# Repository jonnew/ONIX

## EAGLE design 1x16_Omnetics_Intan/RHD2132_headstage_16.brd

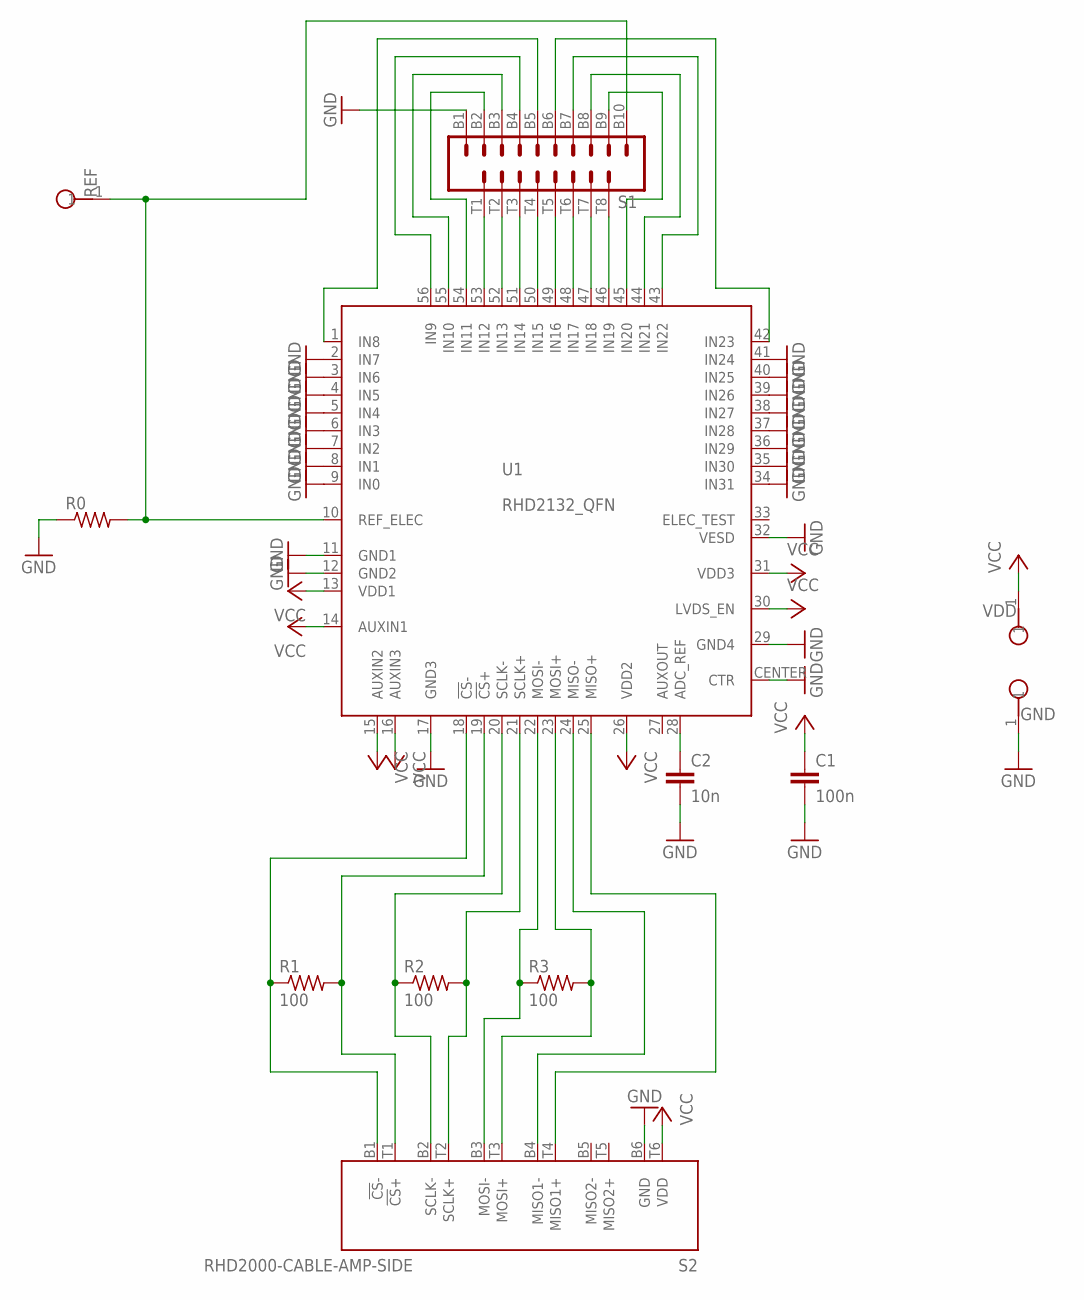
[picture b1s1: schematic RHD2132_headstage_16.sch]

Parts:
C1: 100n; 0402
C2: 10n; 0402
GND: TESTPOINT_SMALL
R0: R_0402; 0402
R1, R2, R3: 100; 0402
REF: TESTPOINT_SMALL
S1: OMNETICS_A79041
S2: RHD2000-CABLE-AMP-SIDE; OMNETICS_PZN-12-AA
U1: RHD2132_QFN; QFN56_8_X_8_LARGE
VDD: TESTPOINT_SMALL

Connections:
GND: C1.2, C2.2, GND.1, R0.1, S1.B1, S2.B6 (GND), U1.2 (IN7), U1.3 (IN6), U1.4 (IN5), U1.5 (IN4), U1.6 (IN3), U1.7 (IN2), U1.8 (IN1), U1.9 (IN0), U1.11 (GND1), U1.12 (GND2), U1.17 (GND3), U1.29 (GND4), U1.32 (VESD), U1.34 (IN31), U1.35 (IN30), U1.36 (IN29), U1.37 (IN28), U1.38 (IN27), U1.39 (IN26), U1.40 (IN25), U1.41 (IN24), U1.CENTER (CTR)
unnamed: R0.2, REF.1, S1.B10, U1.10 (REF_ELEC)
unnamed: S1.B6, U1.42 (IN23)
unnamed: R1.1, S2.B1 (!CS!-), U1.18 (!CS!-)
unnamed: S1.T4, U1.50 (IN15)
unnamed: S1.T3, U1.51 (IN14)
unnamed: S1.T2, U1.52 (IN13)
unnamed: S1.B4, U1.56 (IN9)
unnamed: S1.B3, U1.55 (IN10)
unnamed: S1.B2, U1.54 (IN11)
unnamed: S1.T1, U1.53 (IN12)
unnamed: S1.T5, U1.49 (IN16)
unnamed: S1.T6, U1.48 (IN17)
unnamed: S1.T7, U1.47 (IN18)
unnamed: S1.T8, U1.46 (IN19)
unnamed: S1.B9, U1.45 (IN20)
unnamed: S1.B8, U1.44 (IN21)
unnamed: S1.B7, U1.43 (IN22)
unnamed: S1.B5, U1.1 (IN8)
unnamed: R1.2, S2.T1 (!CS!+), U1.19 (!CS!+)
unnamed: R2.1, S2.B2 (SCLK-), U1.20 (SCLK-)
unnamed: R2.2, S2.T2 (SCLK+), U1.21 (SCLK+)
unnamed: R3.1, S2.B3 (MOSI-), U1.22 (MOSI-)
unnamed: R3.2, S2.T3 (MOSI+), U1.23 (MOSI+)
unnamed: S2.B4 (MISO1-), U1.24 (MISO-)
unnamed: S2.T4 (MISO1+), U1.25 (MISO+)
unnamed: C2.1, U1.28 (ADC_REF)
VCC: C1.1, S2.T6 (VDD), U1.13 (VDD1), U1.14 (AUXIN1), U1.15 (AUXIN2), U1.16 (AUXIN3), U1.26 (VDD2), U1.30 (LVDS_EN), U1.31 (VDD3), VDD.1

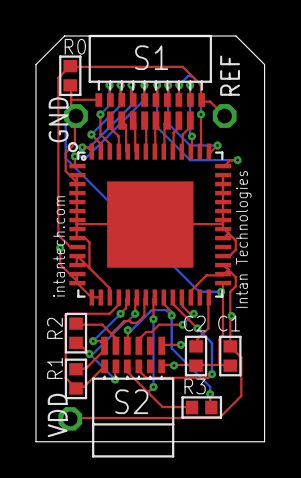
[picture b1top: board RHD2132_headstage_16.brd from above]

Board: 4 copper layers, 12.7 x 22.5 mm, 12 parts (0 on the bottom side), 28 nets.

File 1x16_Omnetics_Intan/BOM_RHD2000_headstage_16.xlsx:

Bill of Materials |  | RHD2000 Headstage Board 16 |  | Intan Technologies, LLC
Part | Value | Device | Package | Digi-Key part number | Notes
C1 | 100 nF (0.1 uF) | ceramic capacitor (25 V) | 0402 | 445-4964-1-ND
C2 | 10 nF (10000 pF) | ceramic capacitor (25 V) | 0402 | 490-1312-1-ND
R0 | 0 | resistor | 0402 | P0.0JCT-ND
R1 | 100 | resistor | 0402 | P100JCT-ND
R2 | 100 | resistor | 0402 | P100JCT-ND
R3 | 100 | resistor | 0402 | P100JCT-ND
S1 | NSD-18-AA-GS | nano strip connector | 18-pin, 2 guides | Omnetics A79041-001
S2 | PZN-12-AA | polarized nano connector | polarized 12-pin | Omnetics A79623-001
U1 | RHD2132 | 32-channel amplifier chip | QFN-56L | Intan RHD2132

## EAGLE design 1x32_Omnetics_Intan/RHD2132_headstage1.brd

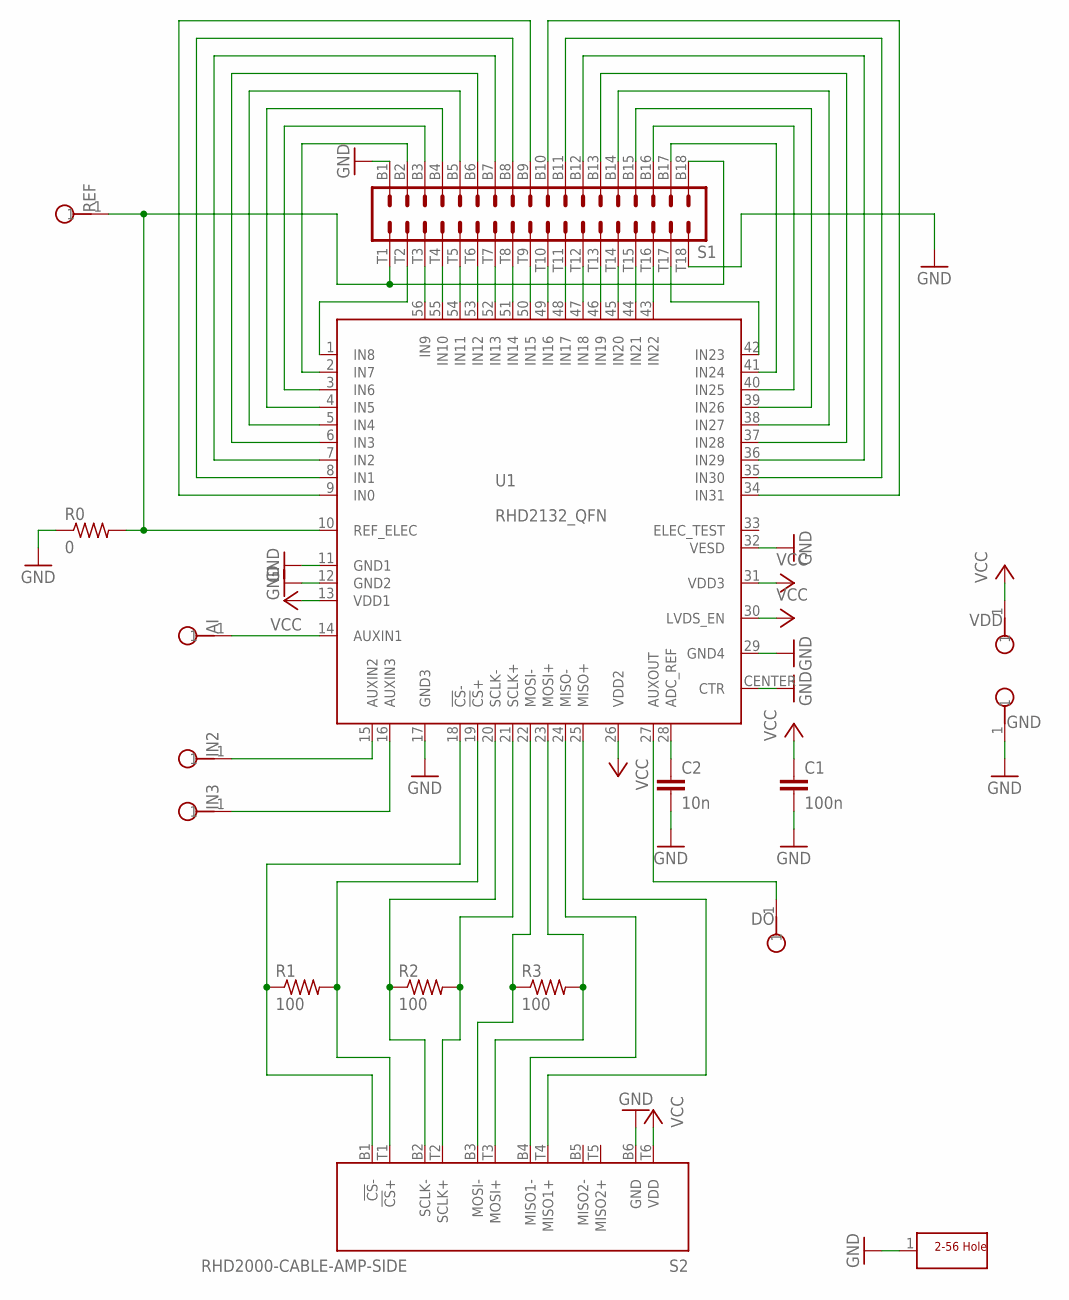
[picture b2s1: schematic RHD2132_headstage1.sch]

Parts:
AI: TESTPOINT_SMALL
C1: 100n; 0402
C2: 10n; 0402
DO: TESTPOINT_SMALL
GND: TESTPOINT_SMALL
H1: SCREW_HOLE_2-56
IN2, IN3: TESTPOINT_SMALL
R0: 0; 0402
R1, R2, R3: 100; 0402
REF: TESTPOINT_SMALL
S1: OMNETICS_A79025
S2: RHD2000-CABLE-AMP-SIDE; OMNETICS_PZN-12-AA
U1: RHD2132_QFN; QFN56_8_X_8_LARGE
VDD: TESTPOINT_SMALL

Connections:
GND: C1.2, C2.2, GND.1, H1.1, R0.1, S1.B1, S1.T18, S2.B6 (GND), U1.11 (GND1), U1.12 (GND2), U1.17 (GND3), U1.29 (GND4), U1.32 (VESD), U1.CENTER (CTR)
unnamed: R0.2, REF.1, S1.B18, S1.T1, U1.10 (REF_ELEC)
unnamed: S1.B3, U1.3 (IN6)
unnamed: S1.B2, U1.2 (IN7)
unnamed: S1.B4, U1.4 (IN5)
unnamed: S1.B5, U1.5 (IN4)
unnamed: S1.B6, U1.6 (IN3)
unnamed: S1.B7, U1.7 (IN2)
unnamed: S1.B8, U1.8 (IN1)
unnamed: S1.B9, U1.9 (IN0)
unnamed: S1.B10, U1.34 (IN31)
unnamed: R1.1, S2.B1 (!CS!-), U1.18 (!CS!-)
unnamed: S1.B17, U1.41 (IN24)
unnamed: S1.B16, U1.40 (IN25)
unnamed: S1.B15, U1.39 (IN26)
unnamed: S1.B14, U1.38 (IN27)
unnamed: S1.B13, U1.37 (IN28)
unnamed: S1.B12, U1.36 (IN29)
unnamed: S1.B11, U1.35 (IN30)
unnamed: S1.T9, U1.50 (IN15)
unnamed: S1.T8, U1.51 (IN14)
unnamed: S1.T7, U1.52 (IN13)
unnamed: S1.T3, U1.56 (IN9)
unnamed: S1.T4, U1.55 (IN10)
unnamed: S1.T5, U1.54 (IN11)
unnamed: S1.T6, U1.53 (IN12)
unnamed: S1.T10, U1.49 (IN16)
unnamed: S1.T11, U1.48 (IN17)
unnamed: S1.T12, U1.47 (IN18)
unnamed: S1.T13, U1.46 (IN19)
unnamed: S1.T14, U1.45 (IN20)
unnamed: S1.T15, U1.44 (IN21)
unnamed: S1.T16, U1.43 (IN22)
unnamed: S1.T2, U1.1 (IN8)
unnamed: S1.T17, U1.42 (IN23)
unnamed: R1.2, S2.T1 (!CS!+), U1.19 (!CS!+)
unnamed: R2.1, S2.B2 (SCLK-), U1.20 (SCLK-)
unnamed: R2.2, S2.T2 (SCLK+), U1.21 (SCLK+)
unnamed: R3.1, S2.B3 (MOSI-), U1.22 (MOSI-)
unnamed: R3.2, S2.T3 (MOSI+), U1.23 (MOSI+)
unnamed: S2.B4 (MISO1-), U1.24 (MISO-)
unnamed: S2.T4 (MISO1+), U1.25 (MISO+)
unnamed: C2.1, U1.28 (ADC_REF)
unnamed: DO.1, U1.27 (AUXOUT)
unnamed: AI.1, U1.14 (AUXIN1)
unnamed: IN2.1, U1.15 (AUXIN2)
unnamed: IN3.1, U1.16 (AUXIN3)
VCC: C1.1, S2.T6 (VDD), U1.13 (VDD1), U1.26 (VDD2), U1.30 (LVDS_EN), U1.31 (VDD3), VDD.1

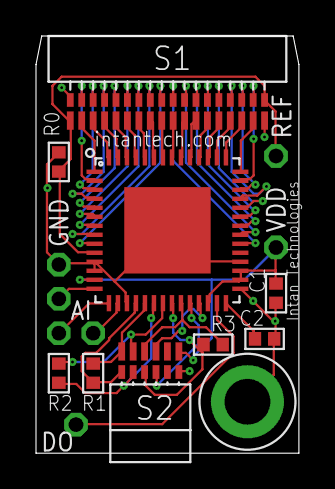
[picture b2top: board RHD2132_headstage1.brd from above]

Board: 4 copper layers, 14.6 x 23.2 mm, 17 parts (0 on the bottom side), 48 nets.

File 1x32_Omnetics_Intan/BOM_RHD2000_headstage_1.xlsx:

Bill of Materials |  | RHD2000 Headstage Board 1 |  | Intan Technologies, LLC
Part | Value | Device | Package | Digi-Key part number | Notes
C1 | 100 nF (0.1 uF) | ceramic capacitor (25 V) | 0402 | 445-4964-1-ND
C2 | 10 nF (10000 pF) | ceramic capacitor (25 V) | 0402 | 490-1312-1-ND
R0 | 0 | resistor | 0402 | P0.0JCT-ND
R1 | 100 | resistor | 0402 | P100JCT-ND
R2 | 100 | resistor | 0402 | P100JCT-ND
R3 | 100 | resistor | 0402 | P100JCT-ND
S1 | NSD-36-AA-GS | nano strip connector | 36-pin, 4 guides | Omnetics A79025-001
S2 | PZN-12-AA | polarized nano connector | polarized 12-pin | Omnetics A79623-001
U1 | RHD2132 or RHD2216 | 32-channel amplifier chip | QFN-56L | Intan RHD2132/RHD2216

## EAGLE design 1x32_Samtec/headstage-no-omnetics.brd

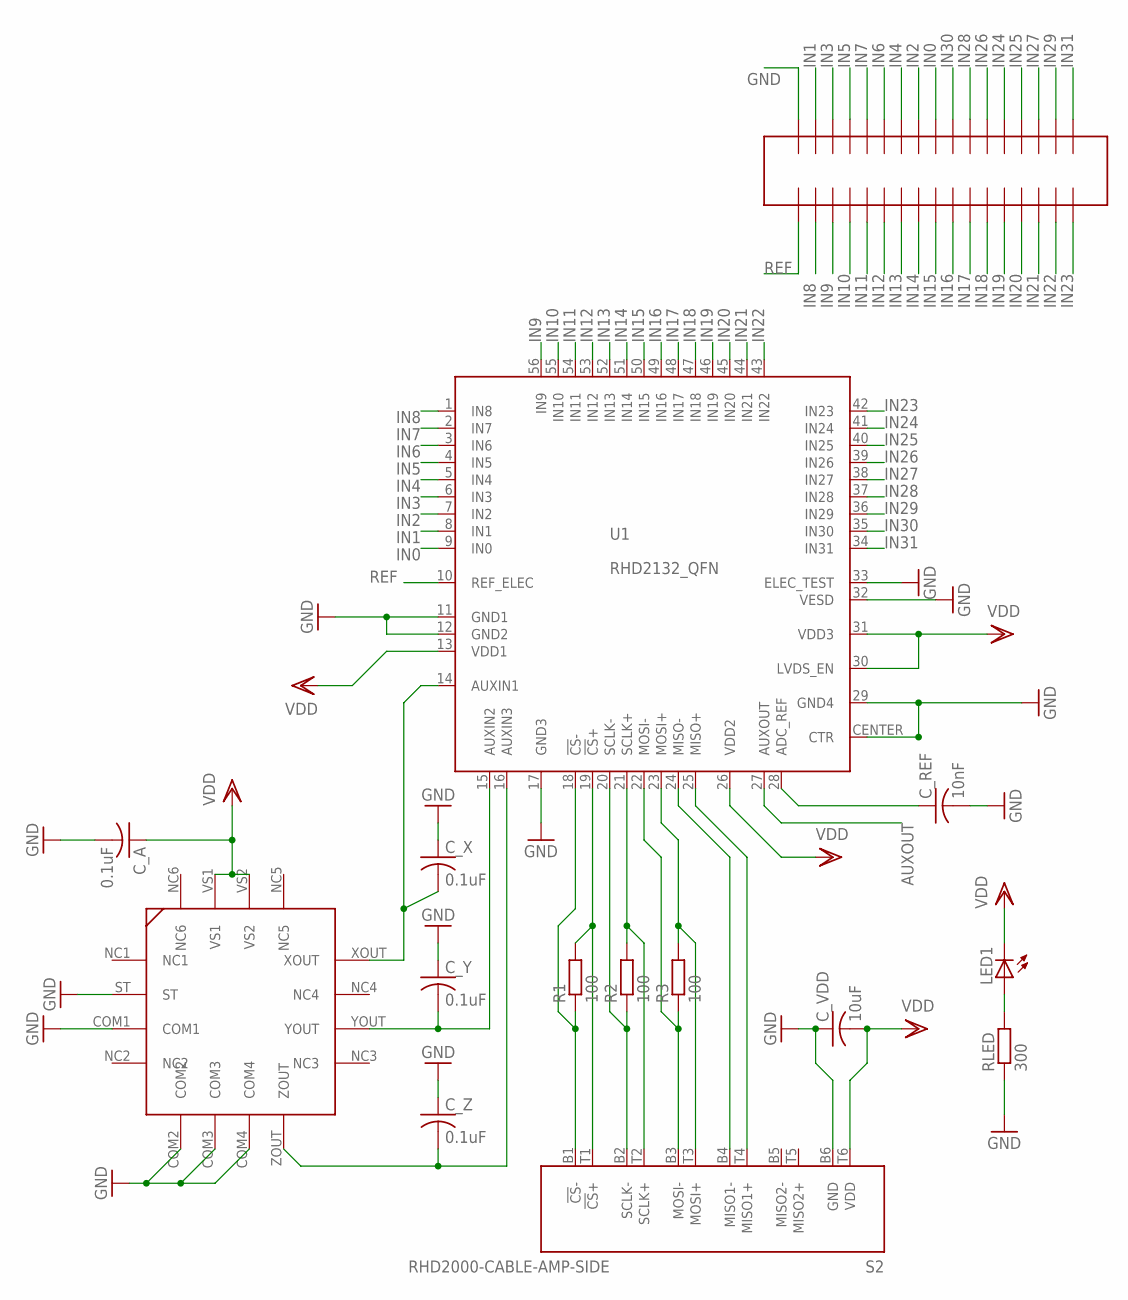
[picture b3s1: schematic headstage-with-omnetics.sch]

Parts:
C_A: 0.1uF; C0402K
C_REF: 10nF; C0402K
C_VDD: 10uF; C0805
C_X: 0.1uF; C0402K
C_Y: 0.1uF; C0402K
C_Z: 0.1uF; C0402K
LED1: LEDCHIPLED_0805; CHIPLED_0805
R1, R2, R3: 100; R0402
RLED: 300; R0402
S2: RHD2000-CABLE-AMP-SIDE; OMNETICS_PZN-12-AA
U1: RHD2132_QFN; QFN56_8_X_8_LARGE
U$1: ADXL335
U$2: FTSH-117BOARD-END; FTSH-117-END

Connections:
ADC_REF: C_REF.1, U1.28 (ADC_REF)
AUXOUT: U1.27 (AUXOUT)
CS+: R1.2, S2.T1 (!CS!+), U1.19 (!CS!+)
CS-: R1.1, S2.B1 (!CS!-), U1.18 (!CS!-)
GND: C_A.2, C_REF.2, C_VDD.1, C_X.1, C_Y.1, C_Z.1, RLED.1, S2.B6 (GND), U1.11 (GND1), U1.12 (GND2), U1.17 (GND3), U1.29 (GND4), U1.32 (VESD), U1.33 (ELEC_TEST), U1.CENTER (CTR), U$1.COM1, U$1.COM2, U$1.COM3, U$1.COM4, U$1.ST, U$2.P$34
IN0: U1.9 (IN0), U$2.P$26
IN1: U1.8 (IN1), U$2.P$33
IN2: U1.7 (IN2), U$2.P$27
IN3: U1.6 (IN3), U$2.P$32
IN4: U1.5 (IN4), U$2.P$28
IN5: U1.4 (IN5), U$2.P$31
IN6: U1.3 (IN6), U$2.P$29
IN7: U1.2 (IN7), U$2.P$30
IN8: U1.1 (IN8), U$2.P$2
IN9: U1.56 (IN9), U$2.P$3
IN10: U1.55 (IN10), U$2.P$4
IN11: U1.54 (IN11), U$2.P$5
IN12: U1.53 (IN12), U$2.P$6
IN13: U1.52 (IN13), U$2.P$7
IN14: U1.51 (IN14), U$2.P$8
IN15: U1.50 (IN15), U$2.P$9
IN16: U1.49 (IN16), U$2.P$10
IN17: U1.48 (IN17), U$2.P$11
IN18: U1.47 (IN18), U$2.P$12
IN19: U1.46 (IN19), U$2.P$13
IN20: U1.45 (IN20), U$2.P$14
IN21: U1.44 (IN21), U$2.P$15
IN22: U1.43 (IN22), U$2.P$16
IN23: U1.42 (IN23), U$2.P$17
IN24: U1.41 (IN24), U$2.P$22
IN25: U1.40 (IN25), U$2.P$21
IN26: U1.39 (IN26), U$2.P$23
IN27: U1.38 (IN27), U$2.P$20
IN28: U1.37 (IN28), U$2.P$24
IN29: U1.36 (IN29), U$2.P$19
IN30: U1.35 (IN30), U$2.P$25
IN31: U1.34 (IN31), U$2.P$18
LEDOUT: LED1.A, RLED.2
MISO1+: S2.T4 (MISO1+), U1.25 (MISO+)
MISO1-: S2.B4 (MISO1-), U1.24 (MISO-)
MOSI+: R3.2, S2.T3 (MOSI+), U1.23 (MOSI+)
MOSI-: R3.1, S2.B3 (MOSI-), U1.22 (MOSI-)
REF: U1.10 (REF_ELEC), U$2.P$1
SCLK+: R2.2, S2.T2 (SCLK+), U1.21 (SCLK+)
SCLK-: R2.1, S2.B2 (SCLK-), U1.20 (SCLK-)
VDD: C_A.1, C_VDD.2, LED1.C, S2.T6 (VDD), U1.13 (VDD1), U1.26 (VDD2), U1.30 (LVDS_EN), U1.31 (VDD3), U$1.VS1, U$1.VS2
XOUT: C_X.2, U1.14 (AUXIN1), U$1.XOUT
YOUT: C_Y.2, U1.15 (AUXIN2), U$1.YOUT
ZOUT: C_Z.2, U1.16 (AUXIN3), U$1.ZOUT

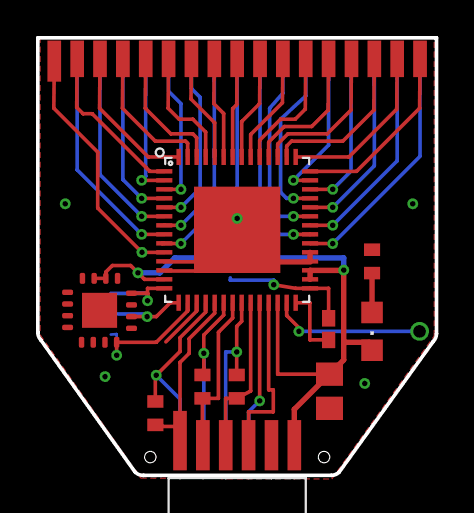
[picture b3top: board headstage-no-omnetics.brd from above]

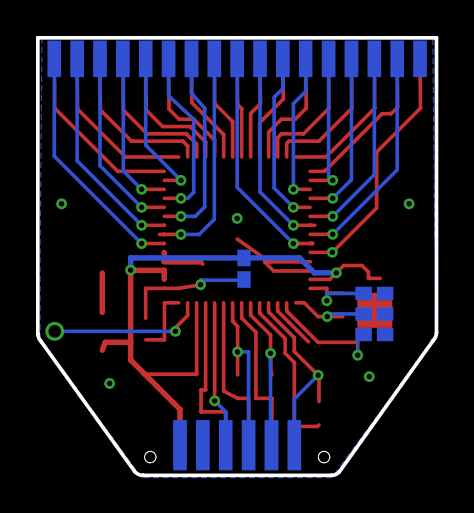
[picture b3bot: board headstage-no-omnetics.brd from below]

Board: 2 copper layers, 22.1 x 24.3 mm, 15 parts (4 on the bottom side), 48 nets.

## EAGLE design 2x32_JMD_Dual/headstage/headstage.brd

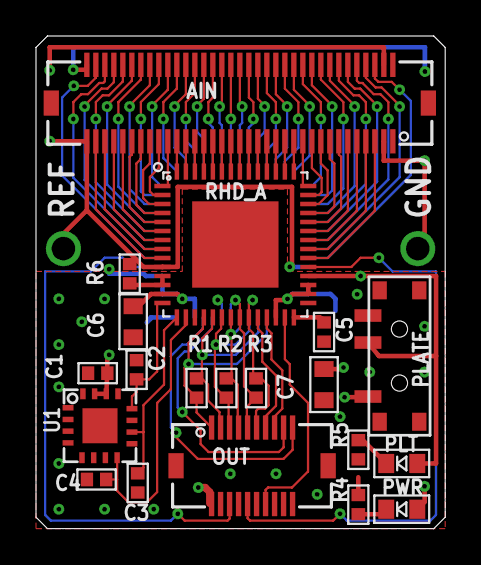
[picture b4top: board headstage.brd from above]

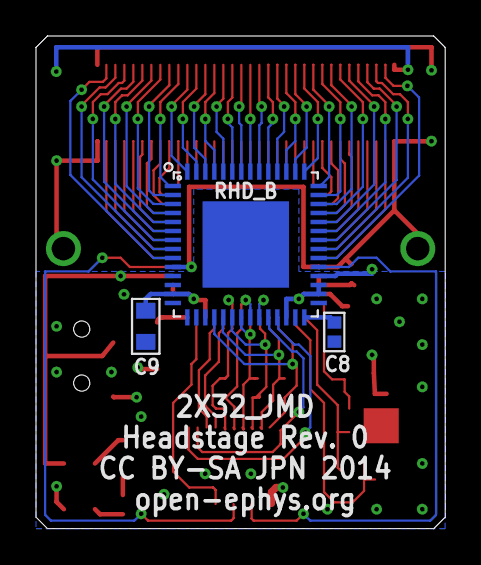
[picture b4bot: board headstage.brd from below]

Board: 4 copper layers, 22.7 x 27.4 mm, 23 parts (3 on the bottom side), 88 nets.

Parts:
AIN: JMD70
C1, C2, C3, C4: .1uF; 0402
C5, C8: 10nF; 0402
C6, C9: .1uF; 0603
C7: 1uF; 0603
OUT: JMD; JMD20-RA
PLATE: PCM12
PLT: RD; CHIP-LED0603
PWR: GR; CHIP-LED0603
R1, R2, R3: 100; 0402
R4, R5: 1k; 0402
R6: 0; 0402
RHD_A: RHD2132_QFN; QFN56_8_X_8_LARGE
RHD_B: RHD2132_QFN; QFN56_8_X_8_LARGE
U1: ADXL335

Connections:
AUXOUT_A: OUT.14, RHD_A.27
CS+: OUT.2, R1.2, RHD_A.19, RHD_B.19
CS-: OUT.1, R1.1, RHD_A.18, RHD_B.18
ELEC_TEST_A: OUT.16, RHD_A.33
ELEC_TEST_B: OUT.18, RHD_B.33
GND: AIN.2, AIN.36, C1.2, C2.1, C3.1, C4.1, C5.2, C6.1, C7.1, C8.2, C9.1, OUT.11, OUT.12, OUT.13, OUT.15, OUT.17, OUT.19, PLATE.3, R4.1, R5.1, R6.1, RHD_A.11, RHD_A.12, RHD_A.17, RHD_A.29, RHD_A.CENTER, RHD_B.11, RHD_B.12, RHD_B.14, RHD_B.15, RHD_B.16, RHD_B.17, RHD_B.29, RHD_B.CENTER, U1.COM1, U1.COM2, U1.COM3, U1.COM4, U1.ST
IN0: AIN.34, RHD_A.9
IN1: AIN.33, RHD_A.8
IN2: AIN.32, RHD_A.7
IN3: AIN.31, RHD_A.6
IN4: AIN.30, RHD_A.5
IN5: AIN.29, RHD_A.4
IN6: AIN.28, RHD_A.3
IN7: AIN.27, RHD_A.2
IN8: AIN.26, RHD_A.1
IN9: AIN.25, RHD_A.56
IN10: AIN.24, RHD_A.55
IN11: AIN.23, RHD_A.54
IN12: AIN.22, RHD_A.53
IN13: AIN.21, RHD_A.52
IN14: AIN.20, RHD_A.51
IN15: AIN.19, RHD_A.50
IN16: AIN.18, RHD_A.49
IN17: AIN.17, RHD_A.48
IN18: AIN.16, RHD_A.47
IN19: AIN.15, RHD_A.46
IN20: AIN.14, RHD_A.45
IN21: AIN.13, RHD_A.44
IN22: AIN.12, RHD_A.43
IN23: AIN.11, RHD_A.42
IN24: AIN.10, RHD_A.41
IN25: AIN.9, RHD_A.40
IN26: AIN.8, RHD_A.39
IN27: AIN.7, RHD_A.38
IN28: AIN.6, RHD_A.37
IN29: AIN.5, RHD_A.36
IN30: AIN.4, RHD_A.35
IN31: AIN.3, RHD_A.34
IN32: AIN.68, RHD_B.9
IN33: AIN.67, RHD_B.8
IN34: AIN.66, RHD_B.7
IN35: AIN.65, RHD_B.6
IN36: AIN.64, RHD_B.5
IN37: AIN.63, RHD_B.4
IN38: AIN.62, RHD_B.3
IN39: AIN.61, RHD_B.2
IN40: AIN.60, RHD_B.1
IN41: AIN.59, RHD_B.56
IN42: AIN.58, RHD_B.55
IN43: AIN.57, RHD_B.54
IN44: AIN.56, RHD_B.53
IN45: AIN.55, RHD_B.52
IN46: AIN.54, RHD_B.51
IN47: AIN.53, RHD_B.50
IN48: AIN.52, RHD_B.49
IN49: AIN.51, RHD_B.48
IN50: AIN.50, RHD_B.47
IN51: AIN.49, RHD_B.46
IN52: AIN.48, RHD_B.45
IN53: AIN.47, RHD_B.44
IN54: AIN.46, RHD_B.43
IN55: AIN.45, RHD_B.42
IN56: AIN.44, RHD_B.41
IN57: AIN.43, RHD_B.40
IN58: AIN.42, RHD_B.39
IN59: AIN.41, RHD_B.38
IN60: AIN.40, RHD_B.37
IN61: AIN.39, RHD_B.36
IN62: AIN.38, RHD_B.35
IN63: AIN.37, RHD_B.34
LEDOUT1: PWR.C, R4.2
LEDOUT2: PLT.C, R5.2
MIS02-: OUT.9, RHD_B.24
MISO1+: OUT.8, RHD_A.25
MISO1-: OUT.7, RHD_A.24
MISO2+: OUT.10, RHD_B.25
MOSI+: OUT.6, R3.2, RHD_A.23, RHD_B.23
MOSI-: OUT.5, R3.1, RHD_A.22, RHD_B.22
unnamed: C8.1, RHD_B.28
unnamed: C5.1, RHD_A.28
REF: AIN.35, AIN.69, R6.2, RHD_A.10, RHD_B.10
SCLK+: OUT.4, R2.2, RHD_A.21, RHD_B.21
SCLK-: OUT.3, R2.1, RHD_A.20, RHD_B.20
VDD: C1.1, C6.2, C7.2, C9.2, OUT.20, PLATE.1, PWR.A, RHD_A.13, RHD_A.26, RHD_A.30, RHD_A.31, RHD_B.13, RHD_B.26, RHD_B.30, RHD_B.31, U1.VS1, U1.VS2
VESD: PLATE.2, PLT.A, RHD_A.32, RHD_B.32
XOUT1: C2.2, RHD_A.14, U1.XOUT
YOUT1: C3.2, RHD_A.15, U1.YOUT
ZOUT1: C4.2, RHD_A.16, U1.ZOUT

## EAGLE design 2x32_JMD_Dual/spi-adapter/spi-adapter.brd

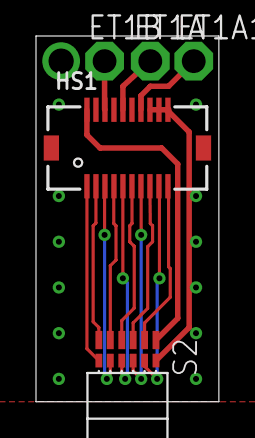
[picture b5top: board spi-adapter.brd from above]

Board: 2 copper layers, 10.2 x 20.3 mm, 5 parts (0 on the bottom side), 15 nets.

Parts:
ET1A, ET1A1, ET1B: TPPAD1-13; P1-13
HS1: JMD20-V
S2: RHD2000-CABLE-AMP-SIDE; OMNETICS_PZN-12-AA

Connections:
AUXOUT_A1: ET1A1.TP, HS1.14
CS_N: HS1.1, S2.B1
CS_P: HS1.2, S2.T1
ELEC_TEST_A1: ET1A.TP, HS1.16
ELEC_TEST_B1: ET1B.TP, HS1.18
GND: HS1.11, HS1.12, HS1.13, HS1.15, HS1.17, HS1.19, S2.B6
MIS02-: HS1.9, S2.B5
MISO1+: HS1.8, S2.T4
MISO1-: HS1.7, S2.B4
MISO2+: HS1.10, S2.T5
MOSI+: HS1.6, S2.T3
MOSI-: HS1.5, S2.B3
SCLK+: HS1.4, S2.T2
SCLK-: HS1.3, S2.B2
VDD: HS1.20, S2.T6

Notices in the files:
2x32_JMD_Dual/headstage/headstage.brd:
CC BY-SA JPN 2014
